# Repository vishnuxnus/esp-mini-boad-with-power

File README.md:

# esp-mini-boad-with-power
ESP8266 basic board with HLK-PM01 power supply

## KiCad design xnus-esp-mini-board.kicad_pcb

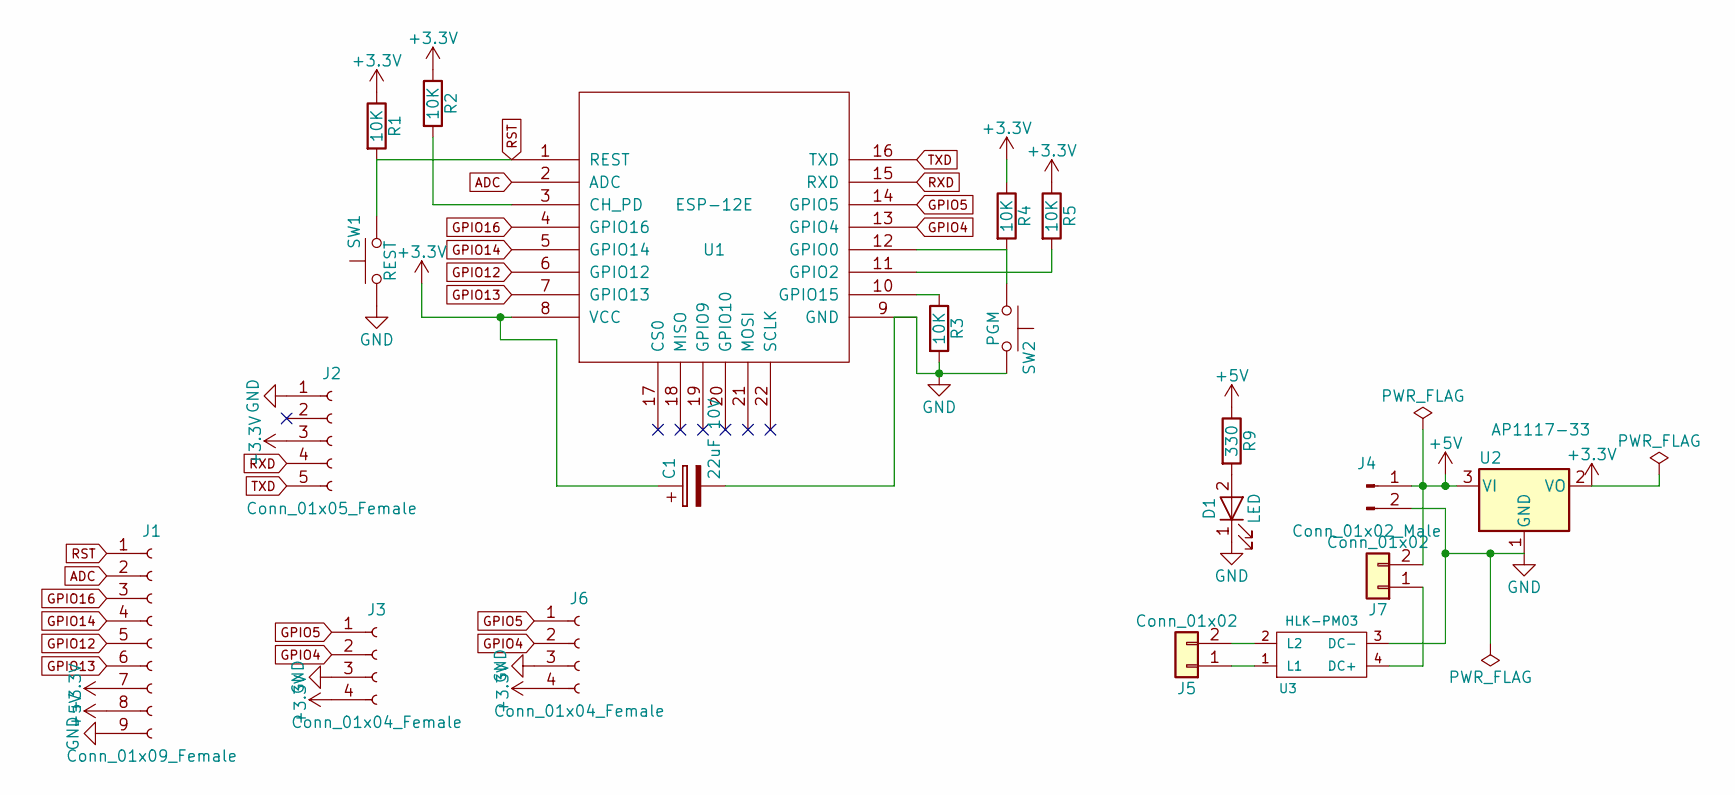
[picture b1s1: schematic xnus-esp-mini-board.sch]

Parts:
C1: 22uF 10V; CP_Radial_D5.0mm_P2.50mm
D1: LED; LED_D1.8mm_W3.3mm_H2.4mm
J1: Conn_01x09_Female; Pin_Header_Straight_1x09_Pitch2.54mm
J2: Conn_01x05_Female; Pin_Header_Straight_1x05_Pitch2.54mm
J3: Conn_01x04_Female; Pin_Header_Straight_1x04_Pitch2.54mm
J4: Conn_01x02_Male; JST_EH_B02B-EH-A_02x2.50mm_Straight
J5: Conn_01x02; TerminalBlock_bornier-2_P5.08mm
J6: Conn_01x04_Female; JST_EH_B04B-EH-A_04x2.50mm_Straight
J7: Conn_01x02; Pin_Header_Straight_1x02_Pitch2.54mm
R1: 10K; R_Axial_DIN0207_L6.3mm_D2.5mm_P10.16mm_Horizontal
R2, R3, R4, R5: 10K; R_Axial_DIN0207_L6.3mm_D2.5mm_P5.08mm_Vertical
R9: 330; R_Axial_DIN0207_L6.3mm_D2.5mm_P5.08mm_Vertical
SW1: REST; SW_PUSH_6mm
SW2: PGM; SW_PUSH_6mm
U1: ESP-12E
U2: AP1117-33; SOT-223-3_TabPin2
U3: HLK-PM03; HLK-PM01

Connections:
+3V3: C1.1, J1.7, J2.3, J3.4, J6.4, R1.1, R2.1, R4.1, R5.1, U1.8 (VCC), U2.2 (VO)
+5V: J1.8, J4.1, J7.2, R9.1, U2.3 (VI)
ADC: J1.2, U1.2 (ADC)
GND: C1.2, D1.1 (K), J1.9, J2.1, J3.3, J4.2, J6.3, R3.2, SW1.1, SW2.2, U1.9 (GND), U2.1 (GND), U3.3 (DC-)
GPIO4: J3.2, J6.2, U1.13 (GPIO4)
GPIO5: J3.1, J6.1, U1.14 (GPIO5)
GPIO12: J1.5, U1.6 (GPIO12)
GPIO13: J1.6, U1.7 (GPIO13)
GPIO14: J1.4, U1.5 (GPIO14)
GPIO16: J1.3, U1.4 (GPIO16)
unnamed: D1.2 (A), R9.2
unnamed: J5.1, U3.1 (L1)
unnamed: J5.2, U3.2 (L2)
unnamed: J7.1, U3.4 (DC+)
unnamed: R2.2, U1.3 (CH_PD)
unnamed: R3.1, U1.10 (GPIO15)
unnamed: R4.2, SW2.1, U1.12 (GPIO0)
unnamed: R5.2, U1.11 (GPIO2)
RST: J1.1, R1.2, SW1.2, U1.1 (REST)
RXD: J2.4, U1.15 (RXD)
TXD: J2.5, U1.16 (TXD)

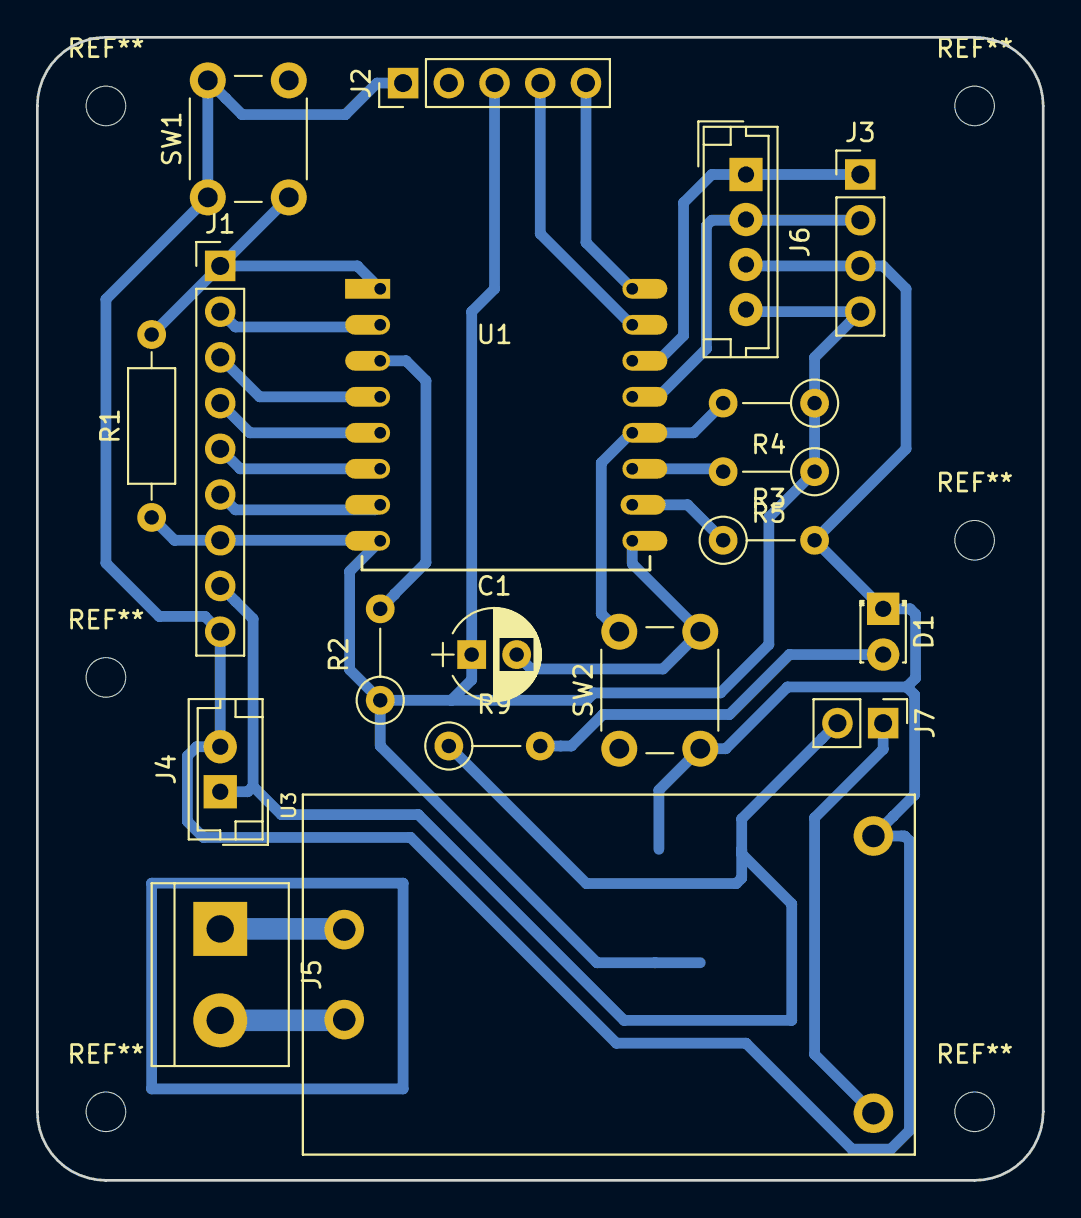
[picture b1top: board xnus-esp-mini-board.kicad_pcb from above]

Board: 2 copper layers, 55.9 x 63.5 mm, 20 parts (1 on the bottom side), 21 nets.
